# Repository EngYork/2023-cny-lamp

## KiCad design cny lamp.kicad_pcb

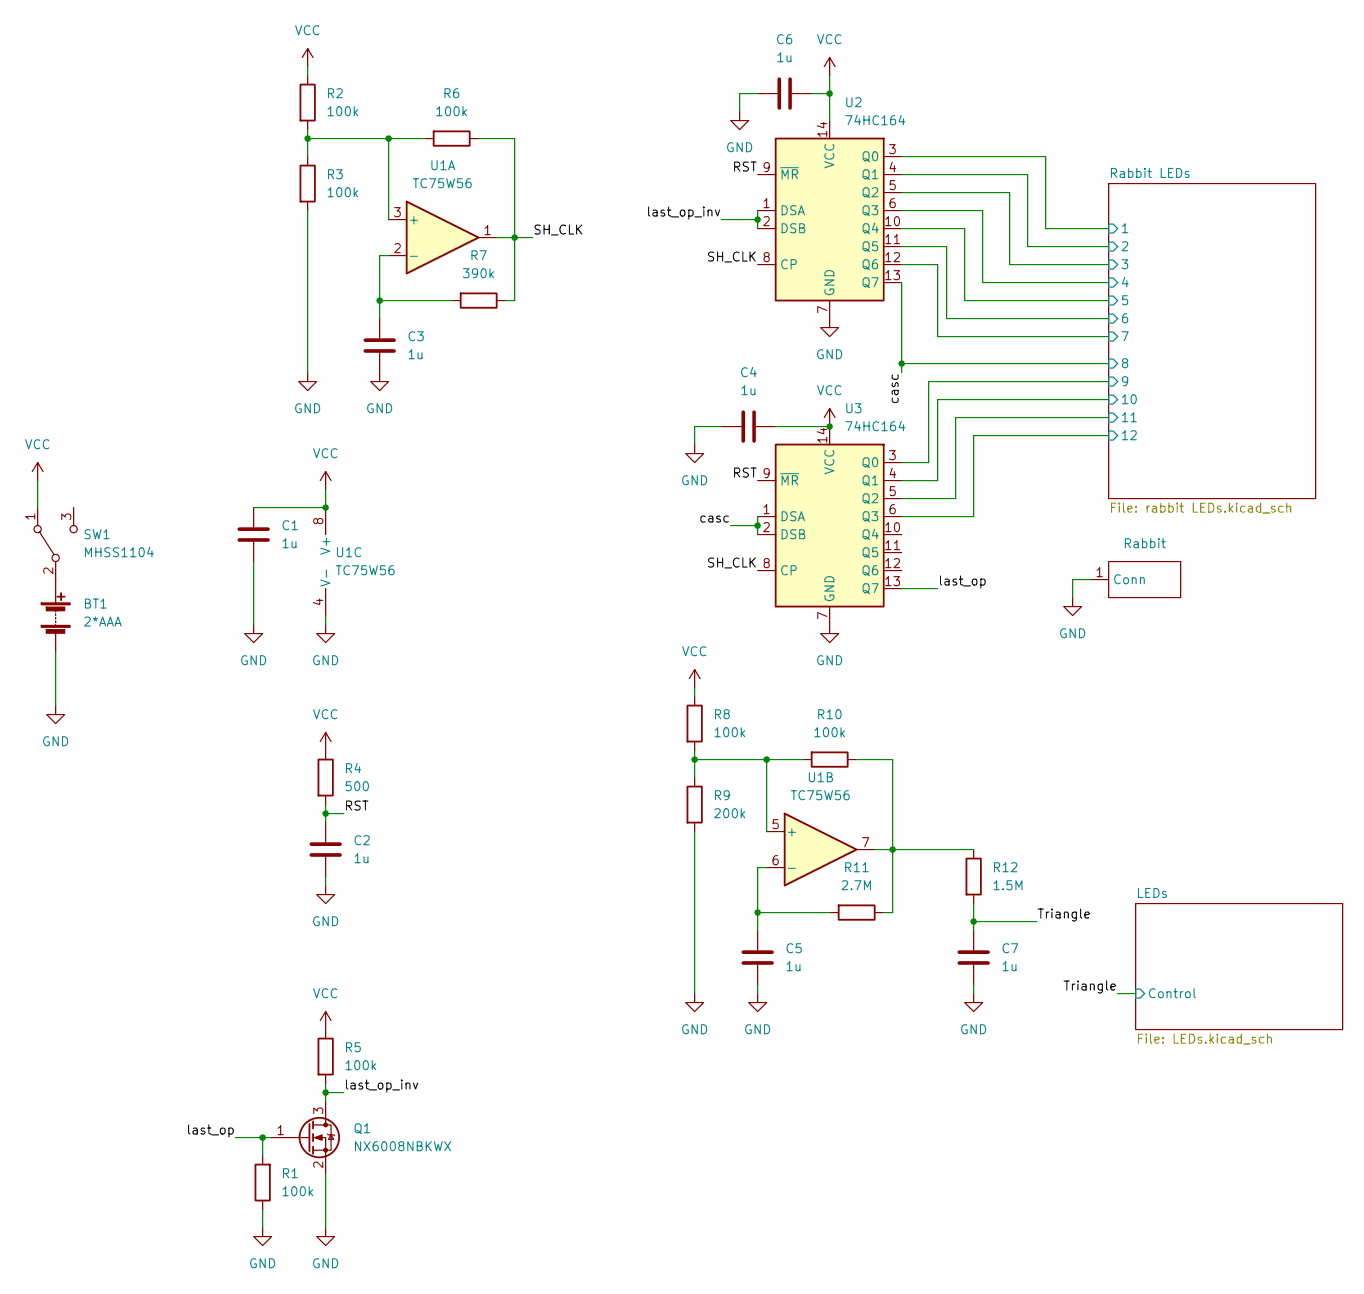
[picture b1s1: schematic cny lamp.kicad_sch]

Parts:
BT1: 2*AAA; BatteryHolder_Keystone_2468_2xAAA
C1, C2, C3, C4, C5, C6, C7: 1u; C_1206_3216Metric_Pad1.33x1.80mm_HandSolder
Q1: NX6008NBKWX; SOT-323_SC-70_Handsoldering
R1, R2, R3, R5, R6, R8, R10: 100k; R_1206_3216Metric_Pad1.30x1.75mm_HandSolder
R4: 500; R_1206_3216Metric_Pad1.30x1.75mm_HandSolder
R7: 390k; R_1206_3216Metric_Pad1.30x1.75mm_HandSolder
R9: 200k; R_1206_3216Metric_Pad1.30x1.75mm_HandSolder
R11: 2.7M; R_1206_3216Metric_Pad1.30x1.75mm_HandSolder
R12: 1.5M; R_1206_3216Metric_Pad1.30x1.75mm_HandSolder
SW1: MHSS1104
U1: TC75W56; VSSOP-8_2.3x2mm_P0.5mm
U2, U3: 74HC164; SOIC-14_3.9x8.7mm_P1.27mm
U4: Rabbit

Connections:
/RST: C2.1, R4.2, U2.9 (~MR), U3.9 (~MR)
/Rabbit LEDs/1: U2.3 (Q0); also elsewhere on the board
/Rabbit LEDs/2: U2.4 (Q1); also elsewhere on the board
/Rabbit LEDs/3: U2.5 (Q2); also elsewhere on the board
/Rabbit LEDs/4: U2.6 (Q3); also elsewhere on the board
/Rabbit LEDs/5: U2.10 (Q4); also elsewhere on the board
/Rabbit LEDs/6: U2.11 (Q5); also elsewhere on the board
/Rabbit LEDs/7: U2.12 (Q6); also elsewhere on the board
/Rabbit LEDs/9: U3.3 (Q0); also elsewhere on the board
/Rabbit LEDs/10: U3.4 (Q1); also elsewhere on the board
/Rabbit LEDs/11: U3.5 (Q2); also elsewhere on the board
/Rabbit LEDs/12: U3.6 (Q3); also elsewhere on the board
/SH_CLK: R6.1, R7.1, U1.1, U2.8 (CP), U3.8 (CP)
/Triangle: C7.1, R12.2; also elsewhere on the board
/casc: U2.13 (Q7), U3.1 (DSA), U3.2 (DSB); also elsewhere on the board
/last_op: Q1.1 (G), R1.2, U3.13 (Q7)
/last_op_inv: Q1.3 (D), R5.2, U2.1 (DSA), U2.2 (DSB)
GND: BT1.2 (-), C1.2, C2.2, C3.2, C4.1, C5.2, C6.1, C7.2, Q1.2 (S), R1.1, R3.2, R9.2, U1.4 (V-), U2.7 (GND), U3.7 (GND), U4.1 (Conn); also elsewhere on the board
unnamed: BT1.1 (+), SW1.2 (B)
unnamed: C3.1, R7.2, U1.2 (-)
unnamed: C5.1, R11.2, U1.6 (-)
unnamed: R2.2, R3.1, R6.2, U1.3 (+)
unnamed: R10.1, R11.1, R12.1, U1.7
unnamed: R8.2, R9.1, R10.2, U1.5 (+)
VCC: C1.1, C4.2, C6.2, R2.1, R4.1, R5.1, R8.1, SW1.1 (A), U1.8 (V+), U2.14 (VCC), U3.14 (VCC); also elsewhere on the board

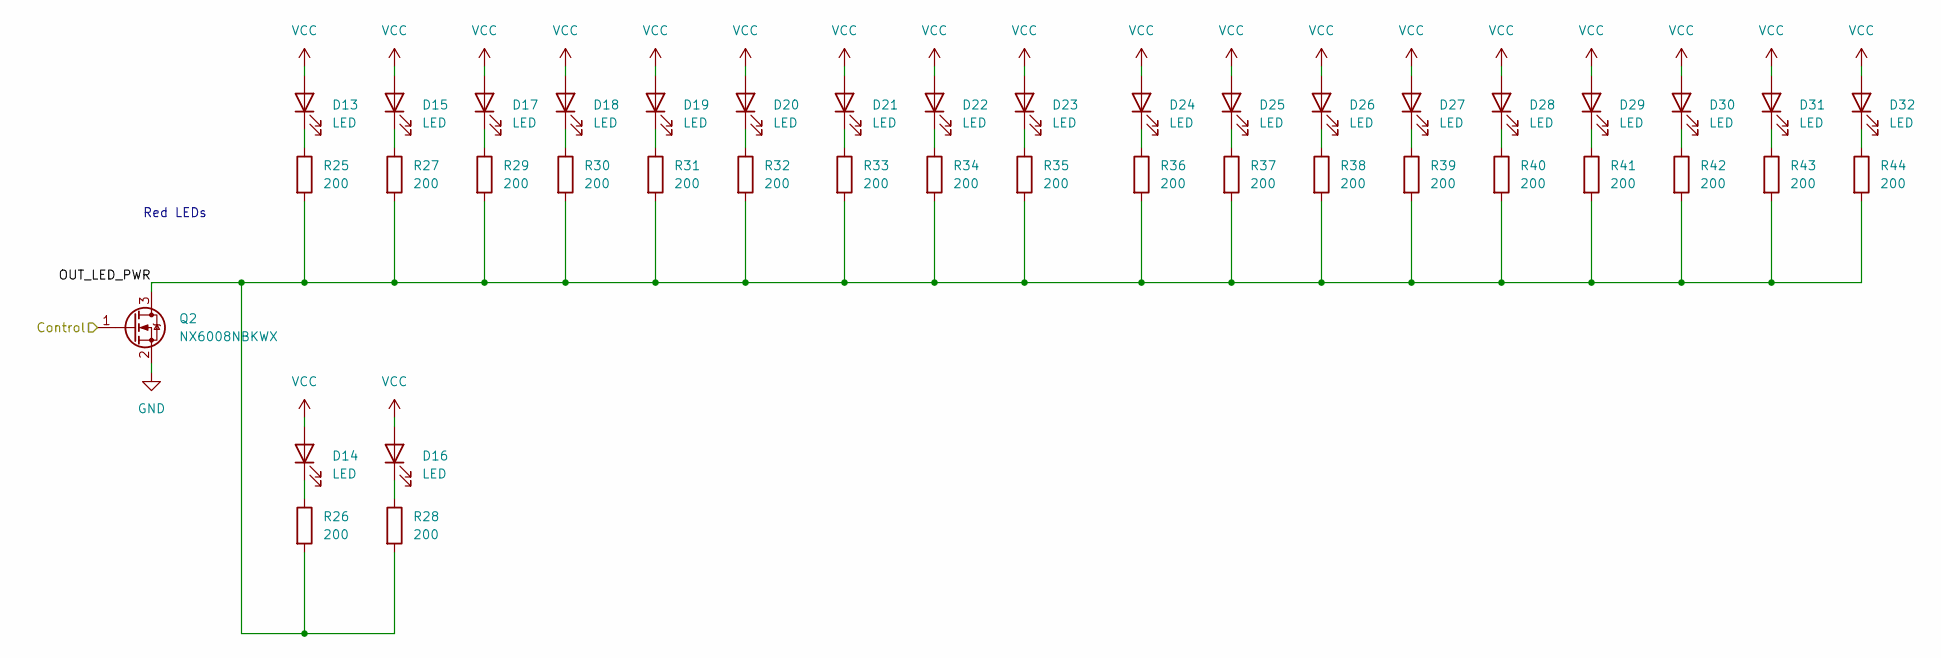
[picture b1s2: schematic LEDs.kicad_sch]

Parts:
D13, D14, D15, D16, D17, D18, D19, D20, D21, D22, D23, D24, D25, D26, D27, D28, D29, D30, D31, D32: LED; LED_D5.0mm
Q2: NX6008NBKWX; SOT-323_SC-70_Handsoldering
R25, R26, R27, R28, R29, R30, R31, R32, R33, R34, R35, R36, R37, R38, R39, R40, R41, R42, R43, R44: 200; R_1206_3216Metric_Pad1.30x1.75mm_HandSolder

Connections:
/LEDs/OUT_LED_PWR: Q2.3 (D), R25.2, R26.2, R27.2, R28.2, R29.2, R30.2, R31.2, R32.2, R33.2, R34.2, R35.2, R36.2, R37.2, R38.2, R39.2, R40.2, R41.2, R42.2, R43.2, R44.2
/Triangle: Q2.1 (G); also elsewhere on the board
GND: Q2.2 (S); also elsewhere on the board
unnamed: D13.1 (K), R25.1
unnamed: D14.1 (K), R26.1
unnamed: D15.1 (K), R27.1
unnamed: D16.1 (K), R28.1
unnamed: D17.1 (K), R29.1
unnamed: D18.1 (K), R30.1
unnamed: D19.1 (K), R31.1
unnamed: D20.1 (K), R32.1
unnamed: D21.1 (K), R33.1
unnamed: D22.1 (K), R34.1
unnamed: D23.1 (K), R35.1
unnamed: D24.1 (K), R36.1
unnamed: D25.1 (K), R37.1
unnamed: D26.1 (K), R38.1
unnamed: D27.1 (K), R39.1
unnamed: D28.1 (K), R40.1
unnamed: D29.1 (K), R41.1
unnamed: D30.1 (K), R42.1
unnamed: D31.1 (K), R43.1
unnamed: D32.1 (K), R44.1
VCC: D13.2 (A), D14.2 (A), D15.2 (A), D16.2 (A), D17.2 (A), D18.2 (A), D19.2 (A), D20.2 (A), D21.2 (A), D22.2 (A), D23.2 (A), D24.2 (A), D25.2 (A), D26.2 (A), D27.2 (A), D28.2 (A), D29.2 (A), D30.2 (A), D31.2 (A), D32.2 (A); also elsewhere on the board

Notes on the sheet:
Red LEDs

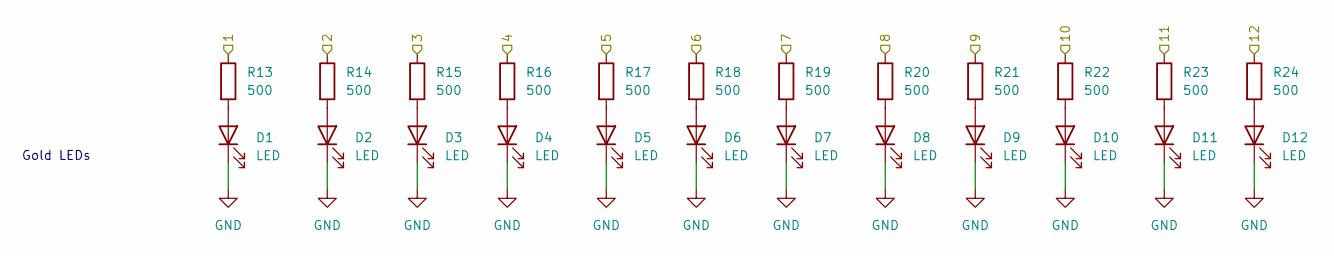
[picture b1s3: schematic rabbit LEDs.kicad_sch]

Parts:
D1, D2, D3, D4, D5, D6, D7, D8, D9, D10, D11, D12: LED; LED_D5.0mm
R13, R14, R15, R16, R17, R18, R19, R20, R21, R22, R23, R24: 500; R_1206_3216Metric_Pad1.30x1.75mm_HandSolder

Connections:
/Rabbit LEDs/1: R13.1; also elsewhere on the board
/Rabbit LEDs/2: R14.1; also elsewhere on the board
/Rabbit LEDs/3: R15.1; also elsewhere on the board
/Rabbit LEDs/4: R16.1; also elsewhere on the board
/Rabbit LEDs/5: R17.1; also elsewhere on the board
/Rabbit LEDs/6: R18.1; also elsewhere on the board
/Rabbit LEDs/7: R19.1; also elsewhere on the board
/Rabbit LEDs/9: R21.1; also elsewhere on the board
/Rabbit LEDs/10: R22.1; also elsewhere on the board
/Rabbit LEDs/11: R23.1; also elsewhere on the board
/Rabbit LEDs/12: R24.1; also elsewhere on the board
/casc: R20.1; also elsewhere on the board
GND: D1.1 (K), D2.1 (K), D3.1 (K), D4.1 (K), D5.1 (K), D6.1 (K), D7.1 (K), D8.1 (K), D9.1 (K), D10.1 (K), D11.1 (K), D12.1 (K); also elsewhere on the board
unnamed: D1.2 (A), R13.2
unnamed: D2.2 (A), R14.2
unnamed: D3.2 (A), R15.2
unnamed: D4.2 (A), R16.2
unnamed: D5.2 (A), R17.2
unnamed: D6.2 (A), R18.2
unnamed: D7.2 (A), R19.2
unnamed: D8.2 (A), R20.2
unnamed: D9.2 (A), R21.2
unnamed: D10.2 (A), R22.2
unnamed: D11.2 (A), R23.2
unnamed: D12.2 (A), R24.2

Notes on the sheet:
Gold LEDs

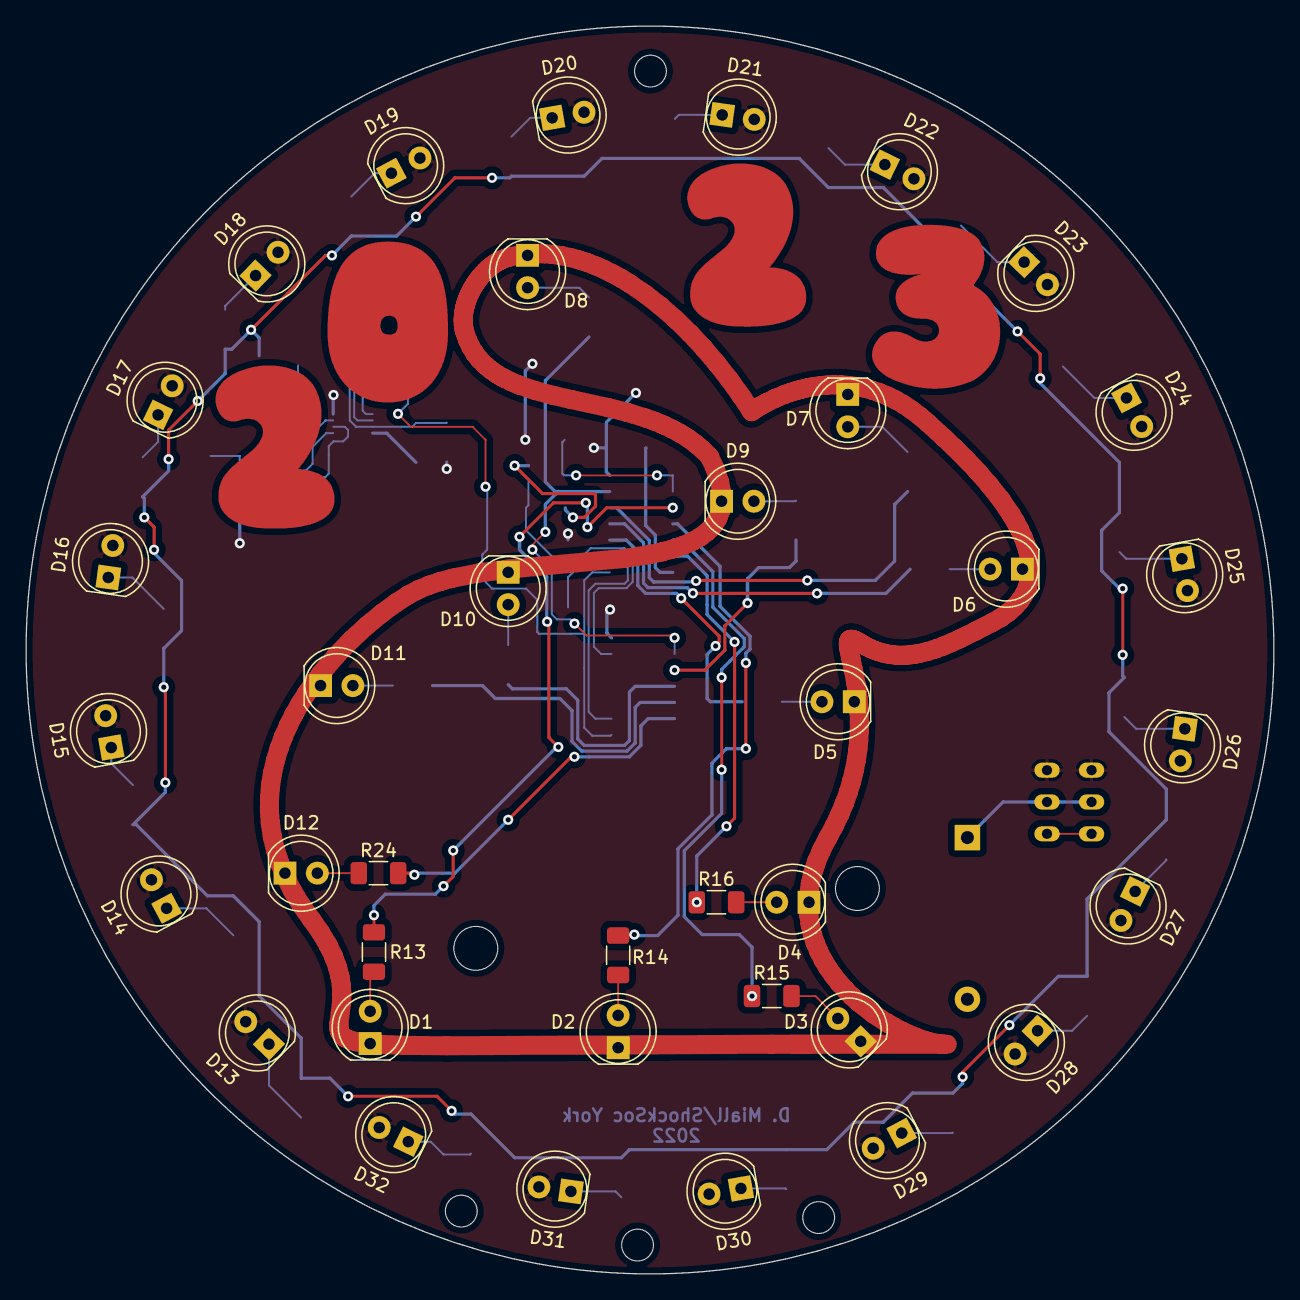
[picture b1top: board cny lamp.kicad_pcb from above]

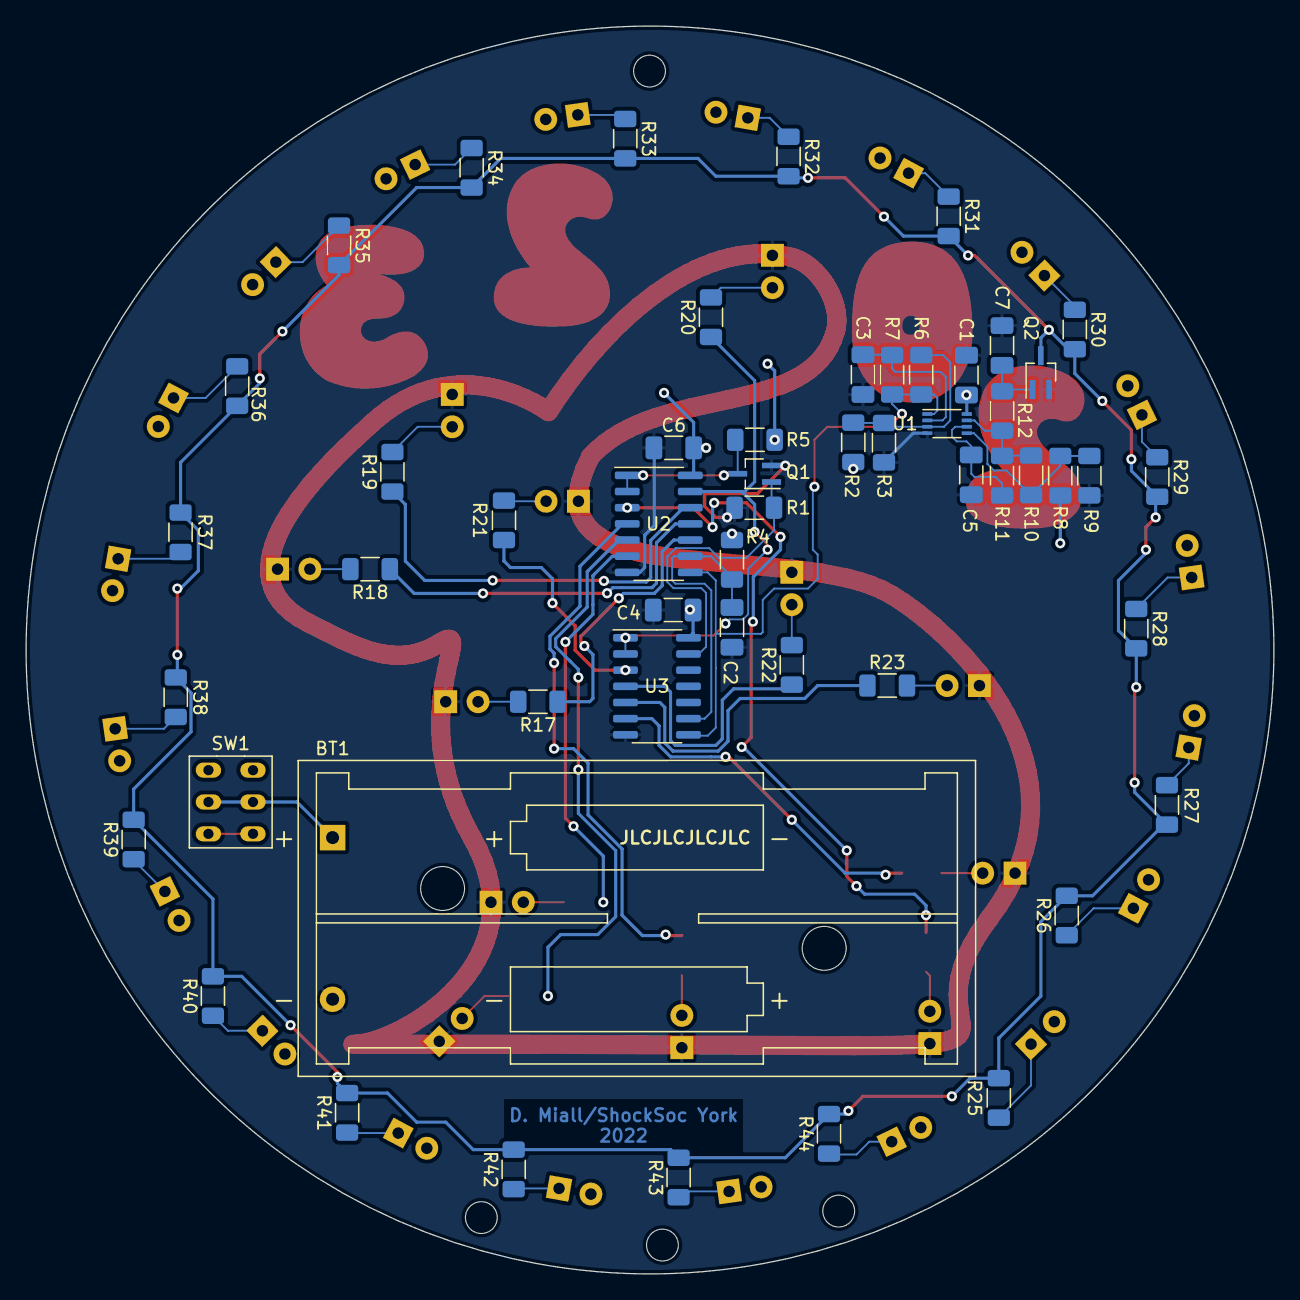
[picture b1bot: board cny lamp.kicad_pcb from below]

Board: 2 copper layers, 98.0 x 98.0 mm, 91 parts (53 on the bottom side), 58 nets.

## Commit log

2022-12-31 Init repo
2022-12-31 gitignore
2022-12-31 Remove schematic -bak
2022-12-31 Label schematic
2023-01-07 Add BoM and complete board
2023-01-07 Add ODS BoM
2023-01-17 Schematic PDF
